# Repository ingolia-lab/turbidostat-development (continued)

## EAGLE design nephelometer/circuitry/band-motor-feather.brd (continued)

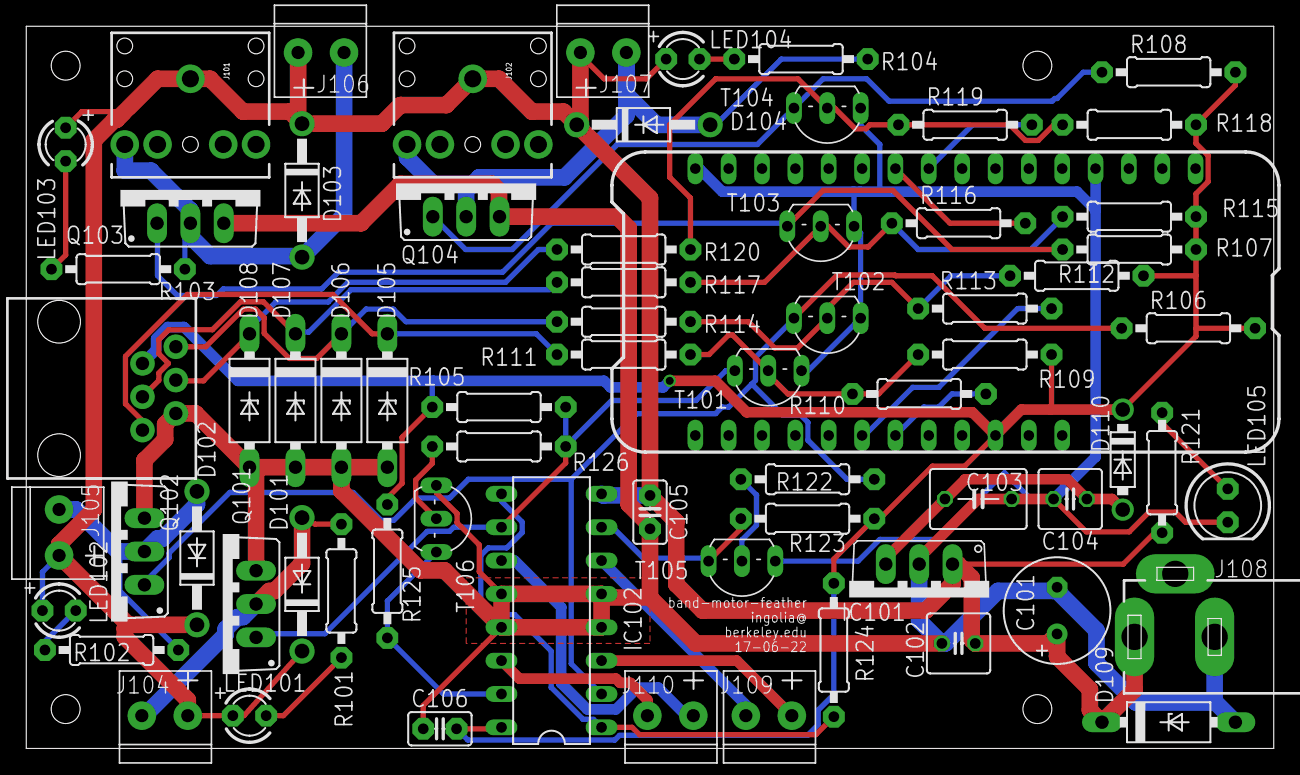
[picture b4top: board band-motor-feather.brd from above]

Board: 2 copper layers, 95.0 x 55.0 mm, 74 parts (0 on the bottom side), 38 nets.

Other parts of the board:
U$3, U$4, U$6, U$7: M2MOUNT

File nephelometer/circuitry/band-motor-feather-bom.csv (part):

"Part";"Value";"Device";"Package";"Description";"DIGIKEY#";"MANF";"MANF#";"MF";"MPN";"OC_FARNELL";"OC_NEWARK";
"C101";"220µF";"CPOL-USE3.5-8";"E3,5-8";"POLARIZED CAPACITOR, American symbol";"P5166-ND";"Panasonic Electronic Components";"ECA-1VM221";"";"";"";"";
"C102";"0.33µ";"C-US025-050X050";"C025-050X050";"CAPACITOR, American symbol";"445-5312-ND ";"TDK Corporation";"FK14X7R1H334K";"";"";"";"";
"C103";"22µ";"C-US050-045X075";"C050-045X075";"CAPACITOR, American symbol";"445-8455-ND";"TDK Corporation";"FK20X7R1C226M";"";"";"";"";
"C104";"0.33µ";"C-US025-050X050";"C025-050X050";"CAPACITOR, American symbol";"445-5312-ND ";"TDK Corporation";"FK14X7R1H334K";"";"";"";"";
"C105";"1µF";"C-US025-025X050";"C025-025X050";"CAPACITOR, American symbol";"445-5318-ND";"TDK Corporation";"FK14X7R1C105K";"";"";"";"";
"C106";"100nF";"C-US025-025X050";"C025-025X050";"CAPACITOR, American symbol";"BC1084CT-ND";"Vishay BC Components";"K104K15X7RF5TL2";"";"";"";"";
"D101";"1N4935";"1N4004";"DO41-10";"DIODE";"1N4935FSCT-ND";"Fairchild Semiconductor";"1N4935";"";"";"";"";
"D102";"1N4935";"1N4004";"DO41-10";"DIODE";"1N4935FSCT-ND";"Fairchild Semiconductor";"1N4935";"";"";"";"";
"D103";"1N4935";"1N4004";"DO41-10";"DIODE";"1N4935FSCT-ND";"Fairchild Semiconductor";"1N4935";"";"";"";"";
"D104";"1N4935";"1N4004";"DO41-10";"DIODE";"1N4935FSCT-ND";"Fairchild Semiconductor";"1N4935";"";"";"";"";
"D105";"";"ZENER-DIODEF126-10";"F126Z10";"Z-Diode";"SA5.0ALFCT-ND";"Littelfuse Inc.";"SA5.0A";"";"";"";"";
"D106";"";"ZENER-DIODEF126-10";"F126Z10";"Z-Diode";"SA5.0ALFCT-ND";"Littelfuse Inc.";"SA5.0A";"";"";"";"";
"D107";"";"ZENER-DIODEF126-10";"F126Z10";"Z-Diode";"SA5.0ALFCT-ND";"Littelfuse Inc.";"SA5.0A";"";"";"";"";
"D108";"";"ZENER-DIODEF126-10";"F126Z10";"Z-Diode";"SA5.0ALFCT-ND";"Littelfuse Inc.";"SA5.0A";"";"";"";"";
"D109";"";"ZENER-DIODEF126-10";"F126Z10";"Z-Diode";"SA12CALFCT-ND";"Littelfuse Inc.";"SA12CA";"";"";"";"";
"D110";"1N5817-T";"1N5817-T";"DO41-7.6";"1.0A SCHOTTKY BARRIER RECTIFIER";"1N5817FSCT-ND";"Fairchild Semiconductor";"1N5817";"";"";"";"";
"IC101";"7805TV";"7805TV";"TO220V";"Positive VOLTAGE REGULATOR";"LM7805CT-ND ";"Fairchild Semiconductor";"LM7805CT";"";"";"";"";
"IC102";"L293D";"L293D";"DIL16";"PUSH-PULL 4 CHANNEL DRIVER";"296-9518-5-ND";"Texas Instruments";"L293DNE";"";"L293D";"9589619";"56P8249";
"IC103";"FEATHER_M0";"FEATHER_M0";"FEATHER_M0";"";"2830-ND";"Adafruit Industries LLC";"2830";"";"";"";"";
"J101";"AUDIO-JACK2PTH";"AUDIO-JACK2PTH";"AUDIO-JACK";"Stereo audio jack with bypass switches.";"CP1-3523N-ND";"CUI Inc.";"SJ1-3523N";"";"";"";"";
"J102";"AUDIO-JACK2PTH";"AUDIO-JACK2PTH";"AUDIO-JACK";"Stereo audio jack with bypass switches.";"CP1-3523N-ND";"CUI Inc.";"SJ1-3523N";"";"";"";"";
"J103";"RJ11-6PTH";"RJ11-6PTH";"RJ11-6";"RJ11 Jack";"AE10383-ND";"Assmann WSW Components";"-2004-1-4-LP-N-R";"";"";"";"";
"J104";"MotA";"1X02_3.5MM_MOT";"1X02_3.5MM_MOT";"";"ED2740-ND";"On Shore Technology Inc.";"OSTTE020104";"";"";"";"";
"J105";"MotA";"1X02_3.5MM_MOT";"1X02_3.5MM_MOT";"";"ED2740-ND";"On Shore Technology Inc.";"OSTTE020104";"";"";"";"";
"J106";"MotA";"1X02_3.5MM_MOT";"1X02_3.5MM_MOT";"";"ED2740-ND";"On Shore Technology Inc.";"OSTTE020104";"";"";"";"";
"J107";"MotA";"1X02_3.5MM_MOT";"1X02_3.5MM_MOT";"";"ED2740-ND";"On Shore Technology Inc.";"OSTTE020104";"";"";"";"";
"J108";"PJ-102A";"PJ-102A";"PJ-102A";"";"CP-102A-ND";"CUI Inc.";"PJ-102A";"";"";"";"";
"J109";"MotA";"1X02_3.5MM_MOT";"1X02_3.5MM_MOT";"";"ED2740-ND";"On Shore Technology Inc.";"OSTTE020104";"";"";"";"";
"J110";"MotA";"1X02_3.5MM_MOT";"1X02_3.5MM_MOT";"";"ED2740-ND";"On Shore Technology Inc.";"OSTTE020104";"";"";"";"";
"LED101";"";"LED3MM";"LED3MM";"LED";"754-1275-ND";"Kingbright";"WP7113SRD/D";"";"";"";"";
"LED102";"";"LED3MM";"LED3MM";"LED";"754-1275-ND";"Kingbright";"WP7113SRD/D";"";"";"";"";
"LED103";"";"LED3MM";"LED3MM";"LED";"754-1275-ND";"Kingbright";"WP7113SRD/D";"";"";"";"";
"LED104";"";"LED3MM";"LED3MM";"LED";"754-1275-ND";"Kingbright";"WP7113SRD/D";"";"";"";"";
"LED105";"";"LED5MM";"LED5MM";"LED";"754-1735-ND";"Kingbright";"WP7113SGD";"";"";"";"";
"Q101";"";"IRLB8721";"TO220BV";"";"IRLB8721PBF-ND";"International Rectifier";"IRLB8721PBF";"";"";"";"";
"Q102";"";"IRLB8721";"TO220BV";"";"IRLB8721PBF-ND";"International Rectifier";"IRLB8721PBF";"";"";"";"";
"Q103";"";"IRLB8721";"TO220BV";"";"IRLB8721PBF-ND";"International Rectifier";"IRLB8721PBF";"";"";"";"";
"Q104";"";"IRLB8721";"TO220BV";"";"IRLB8721PBF-ND";"International Rectifier";"IRLB8721PBF";"";"";"";"";
"R101";"1K5";"R-US_0207/10";"0207/10";"RESISTOR, American symbol";"CF14JT1K50CT-ND";"Stackpole Electronics Inc";"CF14JT330R";"";"";"";"";
"R102";"1K5";"R-US_0207/10";"0207/10";"RESISTOR, American symbol";"CF14JT1K50CT-ND";"Stackpole Electronics Inc";"CF14JT330R";"";"";"";"";
"R103";"1K5";"R-US_0207/10";"0207/10";"RESISTOR, American symbol";"CF14JT1K50CT-ND";"Stackpole Electronics Inc";"CF14JT330R";"";"";"";"";
"R104";"1K5";"R-US_0207/10";"0207/10";"RESISTOR, American symbol";"CF14JT1K50CT-ND";"Stackpole Electronics Inc";"CF14JT330R";"";"";"";"";
"R105";"4K7";"R-US_0207/10";"0207/10";"RESISTOR, American symbol";"CF14JT4K70CT-ND";"Stackpole Electronics Inc";"CF14JT4K70";"";"";"";"";
"R106";"4K7";"R-US_0207/10";"0207/10";"RESISTOR, American symbol";"CF14JT4K70CT-ND";"Stackpole Electronics Inc";"CF14JT4K70";"";"";"";"";
"R107";"4K7";"R-US_0207/10";"0207/10";"RESISTOR, American symbol";"CF14JT4K70CT-ND";"Stackpole Electronics Inc";"CF14JT4K70";"";"";"";"";
"R108";"4K7";"R-US_0207/10";"0207/10";"RESISTOR, American symbol";"CF14JT4K70CT-ND";"Stackpole Electronics Inc";"CF14JT4K70";"";"";"";"";
"R109";"33K";"R-US_0207/10";"0207/10";"RESISTOR, American symbol";"CF14JT33K0CT-ND";"Stackpole Electronics Inc";"CF14JT33K0";"";"";"";"";
"R110";"2K2";"R-US_0207/10";"0207/10";"RESISTOR, American symbol";"CF14JT2K20CT-ND";"Stackpole Electronics Inc";"CF14JT2K20";"";"";"";"";
"R111";"680R";"R-US_0207/10";"0207/10";"RESISTOR, American symbol";"CF14JT680RCT-ND";"Stackpole Electronics Inc";"CF14JT680R";"";"";"";"";
"R112";"33K";"R-US_0207/10";"0207/10";"RESISTOR, American symbol";"CF14JT33K0CT-ND";"Stackpole Electronics Inc";"CF14JT33K0";"";"";"";"";
"R113";"2K2";"R-US_0207/10";"0207/10";"RESISTOR, American symbol";"CF14JT2K20CT-ND";"Stackpole Electronics Inc";"CF14JT2K20";"";"";"";"";
"R114";"680R";"R-US_0207/10";"0207/10";"RESISTOR, American symbol";"CF14JT680RCT-ND";"Stackpole Electronics Inc";"CF14JT680R";"";"";"";"";
"R115";"33K";"R-US_0207/10";"0207/10";"RESISTOR, American symbol";"CF14JT33K0CT-ND";"Stackpole Electronics Inc";"CF14JT33K0";"";"";"";"";
"R116";"2K2";"R-US_0207/10";"0207/10";"RESISTOR, American symbol";"CF14JT2K20CT-ND";"Stackpole Electronics Inc";"CF14JT2K20";"";"";"";"";
"R117";"680R";"R-US_0207/10";"0207/10";"RESISTOR, American symbol";"CF14JT680RCT-ND";"Stackpole Electronics Inc";"CF14JT680R";"";"";"";"";
"R118";"33K";"R-US_0207/10";"0207/10";"RESISTOR, American symbol";"CF14JT33K0CT-ND";"Stackpole Electronics Inc";"CF14JT33K0";"";"";"";"";
"R119";"2K2";"R-US_0207/10";"0207/10";"RESISTOR, American symbol";"CF14JT2K20CT-ND";"Stackpole Electronics Inc";"CF14JT2K20";"";"";"";"";
"R120";"680R";"R-US_0207/10";"0207/10";"RESISTOR, American symbol";"CF14JT680RCT-ND";"Stackpole Electronics Inc";"CF14JT680R";"";"";"";"";
"R121";"1K0";"R-US_0207/9";"0207/9";"RESISTOR, American symbol";"S1KHCT-ND";"Stackpole Electronics Inc.";"CFM12JT1K00";"";"";"";"";
"R122";"33K";"R-US_0207/10";"0207/10";"RESISTOR, American symbol";"CF14JT33K0CT-ND";"Stackpole Electronics Inc";"CF14JT33K0";"";"";"";"";
"R123";"10K";"R-US_0207/10";"0207/10";"RESISTOR, American symbol";"CF14JT10K0CT-ND";"Stackpole Electronics Inc";"CF14JT10K0";"";"";"";"";
"R124";"10K";"R-US_0207/10";"0207/10";"RESISTOR, American symbol";"CF14JT10K0CT-ND";"Stackpole Electronics Inc";"CF14JT10K0";"";"";"";"";
"R125";"10K";"R-US_0207/10";"0207/10";"RESISTOR, American symbol";"CF14JT10K0CT-ND";"Stackpole Electronics Inc";"CF14JT10K0";"";"";"";"";
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
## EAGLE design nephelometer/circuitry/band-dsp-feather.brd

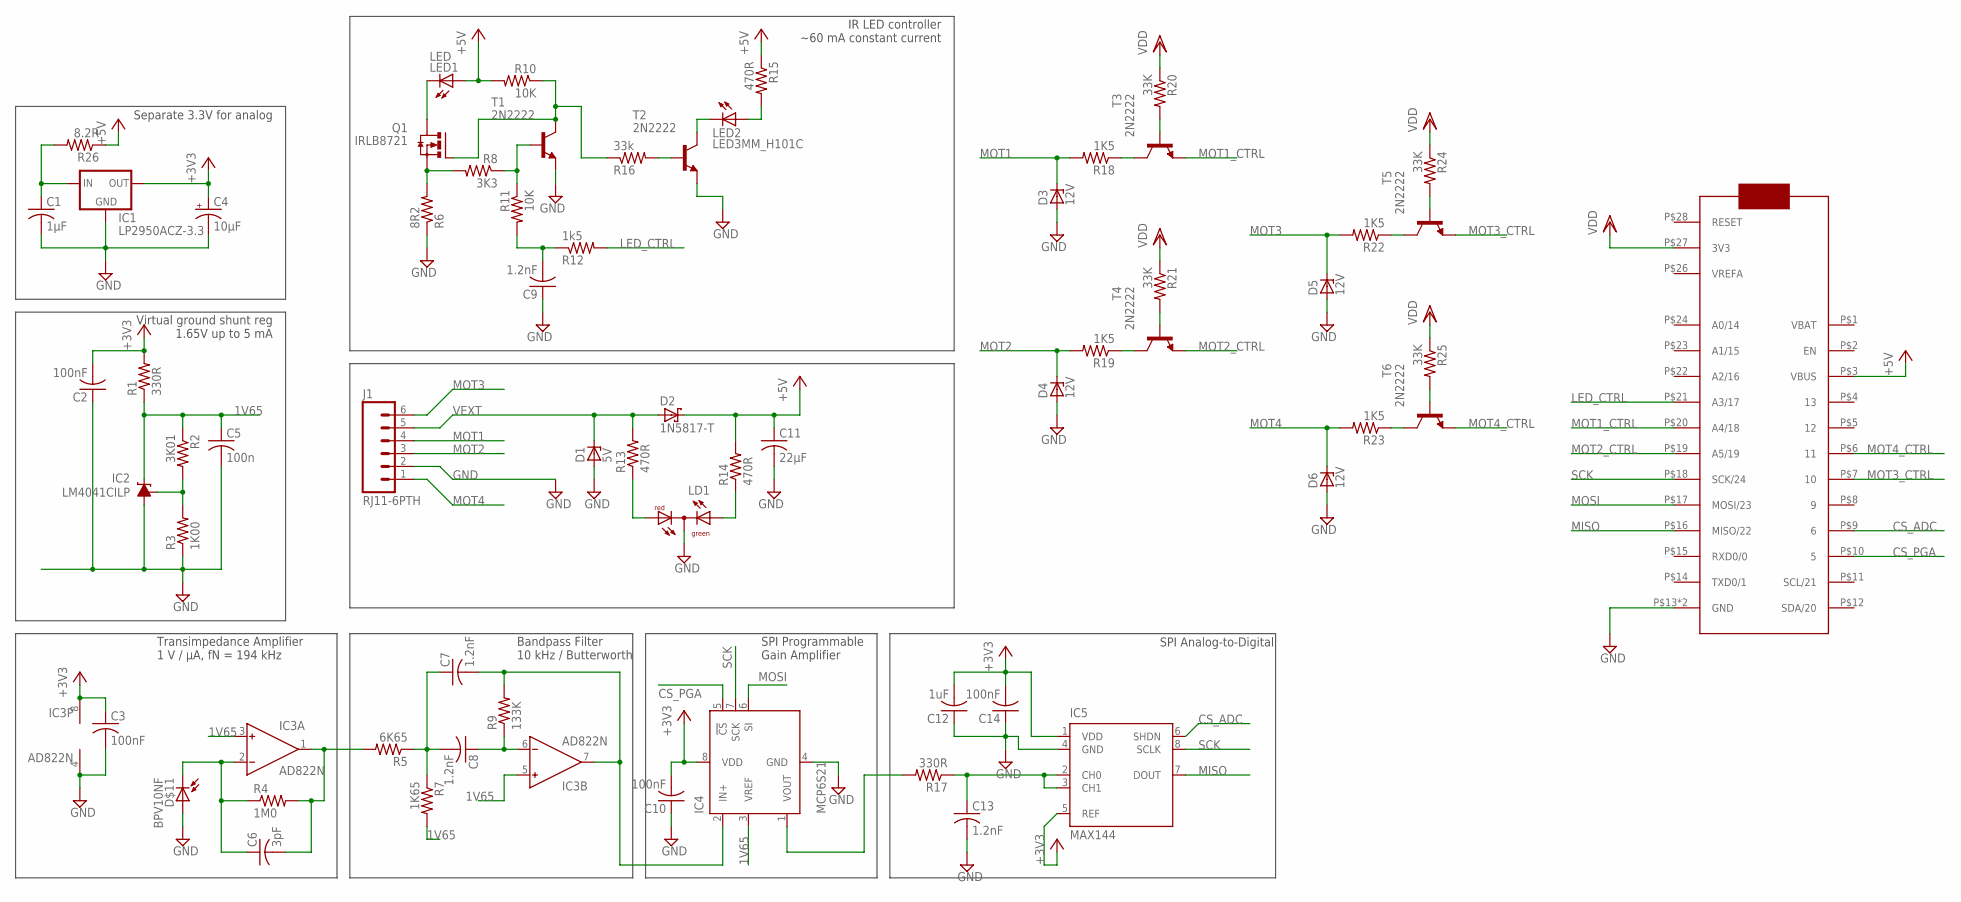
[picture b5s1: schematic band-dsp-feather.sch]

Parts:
C1: 1µF; C025-030X050; DIGIKEY# 445-5318-ND
C2, C3, C10, C14: 100nF; C025-025X050; DIGIKEY# BC1084CT-ND
C4: 10µF; E2,5-5; DIGIKEY# 478-8042-1-ND
C5: 100n; C025-025X050; DIGIKEY# BC1084CT-ND
C6: 3pF; C025-024X044; DIGIKEY# 445-8377-ND
C7, C8, C9, C13: 1.2nF; C025-025X050; DIGIKEY# BC1026CT-ND
C11: 22µF; C050-045X075; DIGIKEY# 445-8455-ND
C12: 1uF; C025-025X050; DIGIKEY# 445-5318-ND
D1: 5V; F126Z10; DIGIKEY# SA5.0ALFCT-ND
D2: 1N5817-T; DO41-7.6; DIGIKEY# 1N5817FSCT-ND
D3, D4, D5, D6: 12V; F126Z10; DIGIKEY# SA12CALFCT-ND
D$11: BPV10NF; LED5MM; DIGIKEY# 751-1002-ND
IC1: LP2950ACZ-3.3; TO92; DIGIKEY# LP2950ACZ-3.3/NOPB-ND
IC2: LM4041CILP; LP_O-PBCY-W3; DIGIKEY# 296-22173-1-ND
IC3: AD822N; DIL08; DIGIKEY# AD823ANZ-ND
IC4: MCP6S21; DIL08; DIGIKEY# MCP6S91-E/P-ND
IC5: MAX144; DIL08; DIGIKEY# MAX144ACPA+-ND
IC6: FEATHER_M0; DIGIKEY# 1528-1531-ND
J1: RJ11-6PTH; RJ11-6; DIGIKEY# AE10383-ND
LD1: DUOLED-RG-C; DUOLED-C-5MM; DIGIKEY# 754-1221-ND
LED1: LED; 1X02_3.5MM; DIGIKEY# 475-3002-ND
LED2: LED3MM_H101C; DIGIKEY# 754-1727-ND
Q1: IRLB8721; TO220BV; DIGIKEY# IRLB8721PBF-ND
R1: 330R; 0207/9; DIGIKEY# CF14JT330RCT-ND
R2: 3K01; 0207/9; DIGIKEY# RNF14FTD3K01CT-ND
R3: 1K00; 0207/9; DIGIKEY# RNF14FTD1K00CT-ND
R4: 1M0; 0207/9; DIGIKEY# RNV14FAL1M00CT-ND
R5: 6K65; 0207/9; DIGIKEY# 6.65KXBK-ND
R6: 8R2; 0207/9; DIGIKEY# S8.2HCT-ND
R7: 1K65; 0207/9; DIGIKEY# 1.65KXBK-ND
R8: 3K3; 0207/9; DIGIKEY# CF14JT3K30CT-ND
R9: 133K; 0207/9; DIGIKEY# 133KXBK-ND
R10, R11: 10K; 0207/9; DIGIKEY# CF14JT10K0CT-ND
R12: 1k5; 0207/9; DIGIKEY# CF14JT1K50CT-ND
R13, R14: 470R; 0207/9; DIGIKEY# CF14JT470RCT-ND
R15: 470R; 0207/5V; DIGIKEY# CF14JT470RCT-ND
R16: 33k; 0207/9; DIGIKEY# CF14JT33K0CT-ND
R17: 330R; 0207/9; DIGIKEY# S330CACT-ND
R18, R19, R22, R23: 1K5; 0207/9; DIGIKEY# CF14JT1K50CT-ND
R20, R21, R24, R25: 33K; 0207/9; DIGIKEY# CF14JT33K0CT-ND
R26: 8.2R; 0207/9; DIGIKEY# S8.2HCT-ND
T1, T2, T3, T4, T5, T6: 2N2222; TO92-EBC-OVAL; DIGIKEY# PN2222ATFCT-ND

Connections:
1V65: C5.1, IC2.2 (C), IC3.3 (IN+), IC3.5 (IN+), IC4.3 (VREF), R1.1, R2.1, R7.2
+3V3: C2.2, C3.1, C4.+, C10.2, C12.2, C14.2, IC1.1 (OUT), IC3.8 (V+), IC4.8 (VDD), IC5.1 (VDD), IC5.5 (REF), R1.2
+5V: C11.1, D2.C, IC6.P$3 (VBUS), LED1.1A (A), R10.2, R14.2, R15.1, R26.1
BPF: C7.2, IC3.7 (OUT), IC4.2 (IN+), R9.2
CS_ADC: IC5.6 (SHDN), IC6.P$9 (6)
CS_PGA: IC4.5 (!CS), IC6.P$10 (5)
FB: C6.1, D$11.K, IC3.2 (IN-), R4.1
GND: C1.2, C2.1, C3.2, C4.-, C5.2, C9.1, C10.1, C11.2, C12.1, C13.2, C14.1, D1.A, D3.A, D4.A, D5.A, D6.A, D$11.A, IC1.2 (GND), IC2.3 (A), IC3.4 (V-), IC4.4 (GND), IC5.4 (GND), IC6.P$13 (GND), IC6.P$25 (GND), J1.2, LD1.C, R3.1, R6.1, T1.E, T2.E
LED_CTRL: IC6.P$21 (A3/17), R12.2
MISO: IC5.7 (DOUT), IC6.P$16 (MISO/22)
MOSI: IC4.6 (SI), IC6.P$17 (MOSI/23)
MOT1: D3.C, J1.4, R18.2
MOT1_CTRL: IC6.P$20 (A4/18), T3.E
MOT2: D4.C, J1.3, R19.2
MOT2_CTRL: IC6.P$19 (A5/19), T4.E
MOT3: D5.C, J1.6, R22.2
MOT3_CTRL: IC6.P$7 (10), T5.E
MOT4: D6.C, J1.1, R23.2
MOT4_CTRL: IC6.P$6 (11), T6.E
unnamed: R19.1, T4.C
unnamed: R21.2, T4.B
unnamed: C7.1, C8.2, R5.1, R7.1
unnamed: IC4.1 (VOUT), R17.2
unnamed: R22.1, T5.C
unnamed: R24.2, T5.B
unnamed: LD1.AX (AG), R14.1
unnamed: Q1.G, R10.1, R16.1, T1.C
unnamed: C8.1, IC3.6 (IN-), R9.1
unnamed: R23.1, T6.C
unnamed: LED2.A, R15.2
unnamed: LED2.K, T2.C
unnamed: R8.1, R11.1, T1.B
unnamed: Q1.S, R6.2, R8.2
unnamed: C9.2, R11.2, R12.1
unnamed: R16.2, T2.B
unnamed: LED1.2K (K), Q1.D
unnamed: R18.1, T3.C
unnamed: R20.2, T3.B
unnamed: R25.2, T6.B
unnamed: LD1.AR, R13.1
unnamed: C13.1, IC5.2 (CH0), IC5.3 (CH1), R17.1
unnamed: C1.1, IC1.3 (IN), R26.2
unnamed: IC2.1 (FB), R2.2, R3.2
SCK: IC4.7 (SCK), IC5.8 (SCLK), IC6.P$18 (SCK/24)
TIA: C6.2, IC3.1 (OUT), R4.2, R5.2
VDD: IC6.P$27 (3V3), R20.1, R21.1, R24.1, R25.1
VEXT: D1.C, D2.A, J1.5, R13.2

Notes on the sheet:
Transimpedance Amplifier 1 V / µA, fN = 194 kHz
Bandpass Filter 10 kHz / Butterworth
Virtual ground shunt reg 1.65V up to 5 mA
IR LED controller ~60 mA constant current
SPI Programmable Gain Amplifier
Separate 3.3V for analog
SPI Analog-to-Digital

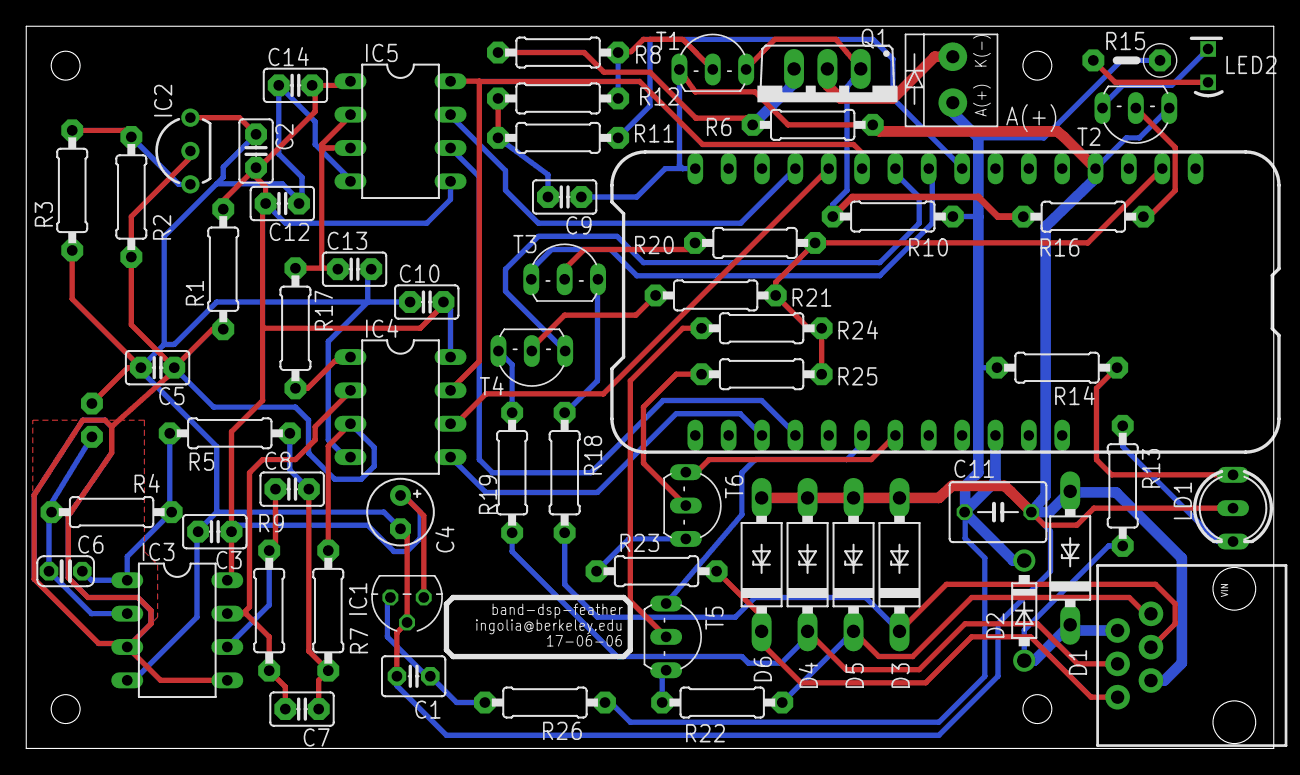
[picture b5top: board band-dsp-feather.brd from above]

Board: 2 copper layers, 95.0 x 55.0 mm, 68 parts (1 on the bottom side), 47 nets.

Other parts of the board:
U$1, U$2, U$3, U$4: M2MOUNT

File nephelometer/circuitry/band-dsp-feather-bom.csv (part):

"Part";"Value";"Device";"Package";"Description";"DIGIKEY#";"DIGIKEY2#";"DIGIKEY3#";"MANF";"MANF#";"MANF2";"MANF2#";"MANF3";"MANF3#";"MF";"MPN";"OC_FARNELL";"OC_NEWARK";
"C1";"1µF";"C-US025-030X050";"C025-030X050";"CAPACITOR, American symbol";"445-5318-ND";"";"";"TDK Corporation";"FK14X7R1C105K";"";"";"";"";"";"";"";"";
"C2";"100nF";"C-US025-025X050";"C025-025X050";"CAPACITOR, American symbol";"BC1084CT-ND";"";"";"Vishay BC Components";"K104K15X7RF5TL2";"";"";"";"";"";"";"";"";
"C3";"100nF";"C-US025-025X050";"C025-025X050";"CAPACITOR, American symbol";"BC1084CT-ND";"";"";"Vishay BC Components";"K104K15X7RF5TL2";"";"";"";"";"";"";"";"";
"C4";"10µF";"CPOL-USE2.5-5";"E2,5-5";"POLARIZED CAPACITOR, American symbol";"478-8042-1-ND";"";"";"AVX Corporation";"TAP106K016SRW";"";"";"";"";"";"";"";"";
"C5";"100n";"C-US025-025X050";"C025-025X050";"CAPACITOR, American symbol";"BC1084CT-ND";"";"";"Vishay BC Components";"K104K15X7RF5TL2";"";"";"";"";"";"";"";"";
"C6";"3pF";"C-US025-024X044";"C025-024X044";"CAPACITOR, American symbol";"445-8377-ND";"";"";"TDK Corporation";"FK18C0G1H030C";"";"";"";"";"";"";"";"";
"C7";"1.2nF";"C-US025-025X050";"C025-025X050";"CAPACITOR, American symbol";"BC1026CT-ND";"";"";"Vishay BC Components";"K122J15C0GF5TL2";"";"";"";"";"";"";"";"";
"C8";"1.2nF";"C-US025-025X050";"C025-025X050";"CAPACITOR, American symbol";"BC1026CT-ND";"";"";"Vishay BC Components";"K122J15C0GF5TL2";"";"";"";"";"";"";"";"";
"C9";"1.2nF";"C-US025-025X050";"C025-025X050";"CAPACITOR, American symbol";"BC1026CT-ND";"";"";"Vishay BC Components";"K122J15C0GF5TL2";"";"";"";"";"";"";"";"";
"C10";"100nF";"C-US025-025X050";"C025-025X050";"CAPACITOR, American symbol";"BC1084CT-ND";"";"";"Vishay BC Components";"K104K15X7RF5TL2";"";"";"";"";"";"";"";"";
"C11";"22µF";"C-US050-045X075";"C050-045X075";"CAPACITOR, American symbol";"445-8455-ND";"";"";"TDK Corporation";"FK20X7R1C226M";"";"";"";"";"";"";"";"";
"C12";"1uF";"C-US025-025X050";"C025-025X050";"CAPACITOR, American symbol";"445-5318-ND";"";"";"TDK Corporation";"FK14X7R1C105K";"";"";"";"";"";"";"";"";
"C13";"1.2nF";"C-US025-025X050";"C025-025X050";"CAPACITOR, American symbol";"BC1026CT-ND";"";"";"Vishay BC Components";"K122J15C0GF5TL2";"";"";"";"";"";"";"";"";
"C14";"100nF";"C-US025-025X050";"C025-025X050";"CAPACITOR, American symbol";"BC1084CT-ND";"";"";"Vishay BC Components";"K104K15X7RF5TL2";"";"";"";"";"";"";"";"";
"D$11";"BPV10NF";"BPV10NF";"LED5MM";"";"751-1002-ND";"";"";"Vishay Semiconductor Opto Division";"BPV10NF";"";"";"";"";"";"";"";"";
"D1";"5V";"ZENER-DIODEF126-10";"F126Z10";"Z-Diode";"SA5.0ALFCT-ND";"";"";"Littelfuse Inc.";"SA5.0A";"";"";"";"";"";"";"";"";
"D2";"1N5817-T";"1N5817-T";"DO41-7.6";"1.0A SCHOTTKY BARRIER RECTIFIER";"1N5817FSCT-ND";"";"";"Fairchild Semiconductor";"1N5817";"";"";"";"";"";"";"";"";
"D3";"12V";"ZENER-DIODEF126-10";"F126Z10";"Z-Diode";"SA12ALFCT-ND";"";"";"Littelfuse Inc.";"SA12A";"";"";"";"";"";"";"";"";
"D4";"12V";"ZENER-DIODEF126-10";"F126Z10";"Z-Diode";"SA12ALFCT-ND";"";"";"Littelfuse Inc.";"SA12A";"";"";"";"";"";"";"";"";
"D5";"12V";"ZENER-DIODEF126-10";"F126Z10";"Z-Diode";"SA12ALFCT-ND";"";"";"Littelfuse Inc.";"SA12A";"";"";"";"";"";"";"";"";
"D6";"12V";"ZENER-DIODEF126-10";"F126Z10";"Z-Diode";"SA12ALFCT-ND";"";"";"Littelfuse Inc.";"SA12A";"";"";"";"";"";"";"";"";
"IC1";"LP2950ACZ-3.3";"LP2950ACZ-3.3";"TO92";"Source: http://cache.national.com/ds/LP/LP2950.pdf";"LP2950ACZ-3.3/NOPB-ND";"";"";"Texas Instruments";"LP2950ACZ-3.3/NOPB";"";"";"";"";"";"";"";"";
"IC2";"LM4041CILP";"LM4041CILP";"LP_O-PBCY-W3";"PRECISION MICROPOWER SHUNT VOLTAGE REFERENCE Adjustable Output";"296-22173-1-ND";"";"";"Texas Instruments";"LM4041CILPR";"";"";"";"";"";"LM4041CILP";"1673945";"50M8856";
"IC3";"AD822N";"AD822N";"DIL08";"Single-Supply, Rail-to-Rail Low Power FET-Input Op Amp";"AD823ANZ-ND";"";"";"Analog Devices Inc.";"AD823ANZ";"";"";"";"";"";"";"1438581";"unknown";
"IC4";"MCP6S21";"MCP6S21";"DIL08";"";"MCP6S91-E/P-ND";"";"";"Microchip Technology";"MCP6S91-E/P";"";"";"";"";"";"";"";"";
"IC5";"MAX144";"MAX144";"DIL08";"";"MAX144ACPA+-ND";"";"";"Maxim Integrated";"MAX144ACPA+";"";"";"";"";"";"";"";"";
"IC6";"FEATHER_M0";"FEATHER_M0";"FEATHER_M0";"";"1528-1531-ND";"2830-ND";"";"Adafruit Industries LLC";"2772";"Adafruit Industries LLC";"2830";"";"";"";"";"";"";
"J1";"RJ11-6PTH";"RJ11-6PTH";"RJ11-6";"RJ11 Jack";"AE10383-ND";"";"";"Assmann WSW Components";"A-2004-1-4-LP-N-R";"";"";"";"";"";"";"";"";
"LD1";"";"DUOLED-RG-C";"DUOLED-C-5MM";"DUO LED";"754-1221-ND";"";"";"Kingbright";"WP3VEGW";"";"";"";"";"";"";"";"";
"LED1";"LED";"1X02_3.5MM_LED";"1X02_3.5MM";"";"475-3002-ND";"492-1502-ND";"ED2740-ND";"OSRAM Opto Semiconductors Inc";"SFH 4547";"Bivar Inc";"CR-174";"On Shore Technology Inc.";"OSTTE020104";"";"";"";"";
"LED2";"LED3MM_H101C";"LED3MM_H101C";"LED3MM_H101C";"";"754-1727-ND";"492-1789-ND";"";"Kingbright";"WP710A10SYD";"Bivar Inc.";"H-101C";"";"";"";"";"";"";
"Q1";"IRLB8721";"IRLB8721";"TO220BV";"";"IRLB8721PBF-ND";"";"";"Infineon Technologies";"IRLB8721PBF";"";"";"";"";"";"";"";"";
"R1";"330R";"R-US_0207/9";"0207/9";"RESISTOR, American symbol";"CF14JT330RCT-ND";"";"";"Stackpole Electronics Inc.";"CF14JT330R";"";"";"";"";"";"";"";"";
"R2";"3K01";"R-US_0207/9";"0207/9";"RESISTOR, American symbol";"RNF14FTD3K01CT-ND";"";"";"Stackpole Electronics Inc.";"RNF14FTD3K01";"";"";"";"";"";"";"";"";
"R3";"1K00";"R-US_0207/9";"0207/9";"RESISTOR, American symbol";"RNF14FTD1K00CT-ND";"";"";"Stackpole Electronics Inc.";"RNF14FTD1K00";"";"";"";"";"";"";"";"";
"R4";"1M0";"R-US_0207/9";"0207/9";"RESISTOR, American symbol";"RNV14FAL1M00CT-ND";"";"";"Stackpole Electronics Inc";"RNV14FAL1M00";"";"";"";"";"";"";"";"";
"R5";"6K65";"R-US_0207/9";"0207/9";"RESISTOR, American symbol";"6.65KXBK-ND";"";"";"Yageo";"MFR-25FBF52-6K65";"";"";"";"";"";"";"";"";
"R6";"8R2";"R-US_0207/9";"0207/9";"RESISTOR, American symbol";"S8.2HCT-ND";"";"";"Stackpole Electronics Inc.";"CFM12JT8R20";"";"";"";"";"";"";"";"";
"R7";"1K65";"R-US_0207/9";"0207/9";"RESISTOR, American symbol";"1.65KXBK-ND";"";"";"Yageo";"MFR-25FBF52-1K65";"";"";"";"";"";"";"";"";
"R8";"3K3";"R-US_0207/9";"0207/9";"RESISTOR, American symbol";"CF14JT3K30CT-ND";"";"";"Stackpole Electronics Inc";"CF14JT3K30";"";"";"";"";"";"";"";"";
"R9";"133K";"R-US_0207/9";"0207/9";"RESISTOR, American symbol";"133KXBK-ND";"";"";"Yageo";"MFR-25FBF52-133K";"";"";"";"";"";"";"";"";
"R10";"10K";"R-US_0207/9";"0207/9";"RESISTOR, American symbol";"CF14JT10K0CT-ND";"";"";"Stackpole Electronics Inc";"CF14JT10K0";"";"";"";"";"";"";"";"";
"R11";"10K";"R-US_0207/9";"0207/9";"RESISTOR, American symbol";"CF14JT10K0CT-ND";"";"";"Stackpole Electronics Inc";"CF14JT10K0";"";"";"";"";"";"";"";"";
"R12";"1k5";"R-US_0207/9";"0207/9";"RESISTOR, American symbol";"CF14JT1K50CT-ND";"";"";"Stackpole Electronics Inc";"CF14JT1K50";"";"";"";"";"";"";"";"";
"R13";"470R";"R-US_0207/9";"0207/9";"RESISTOR, American symbol";"CF14JT470RCT-ND";"";"";"Stackpole Electronics Inc.";"CF14JT470R";"";"";"";"";"";"";"";"";
"R14";"470R";"R-US_0207/9";"0207/9";"RESISTOR, American symbol";"CF14JT470RCT-ND";"";"";"Stackpole Electronics Inc.";"CF14JT470R";"";"";"";"";"";"";"";"";
"R15";"470R";"R-US_0207/5V";"0207/5V";"RESISTOR, American symbol";"CF14JT470RCT-ND";"";"";"Stackpole Electronics Inc.";"CF14JT470R";"";"";"";"";"";"";"";"";
"R16";"33k";"R-US_0207/9";"0207/9";"RESISTOR, American symbol";"CF14JT33K0CT-ND";"";"";"Stackpole Electronics Inc";"CF14JT33K0";"";"";"";"";"";"";"";"";
"R17";"330R";"R-US_0207/9";"0207/9";"RESISTOR, American symbol";"S330CACT-ND";"";"";"Stackpole Electronics Inc.";"RNMF14FTC330R";"";"";"";"";"";"";"";"";
"R18";"1K5";"R-US_0207/9";"0207/9";"RESISTOR, American symbol";"CF14JT1K50CT-ND";"";"";"Stackpole Electronics Inc.";"CF14JT1K50";"";"";"";"";"";"";"";"";
"R19";"1K5";"R-US_0207/9";"0207/9";"RESISTOR, American symbol";"CF14JT1K50CT-ND";"";"";"Stackpole Electronics Inc.";"CF14JT1K50";"";"";"";"";"";"";"";"";
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
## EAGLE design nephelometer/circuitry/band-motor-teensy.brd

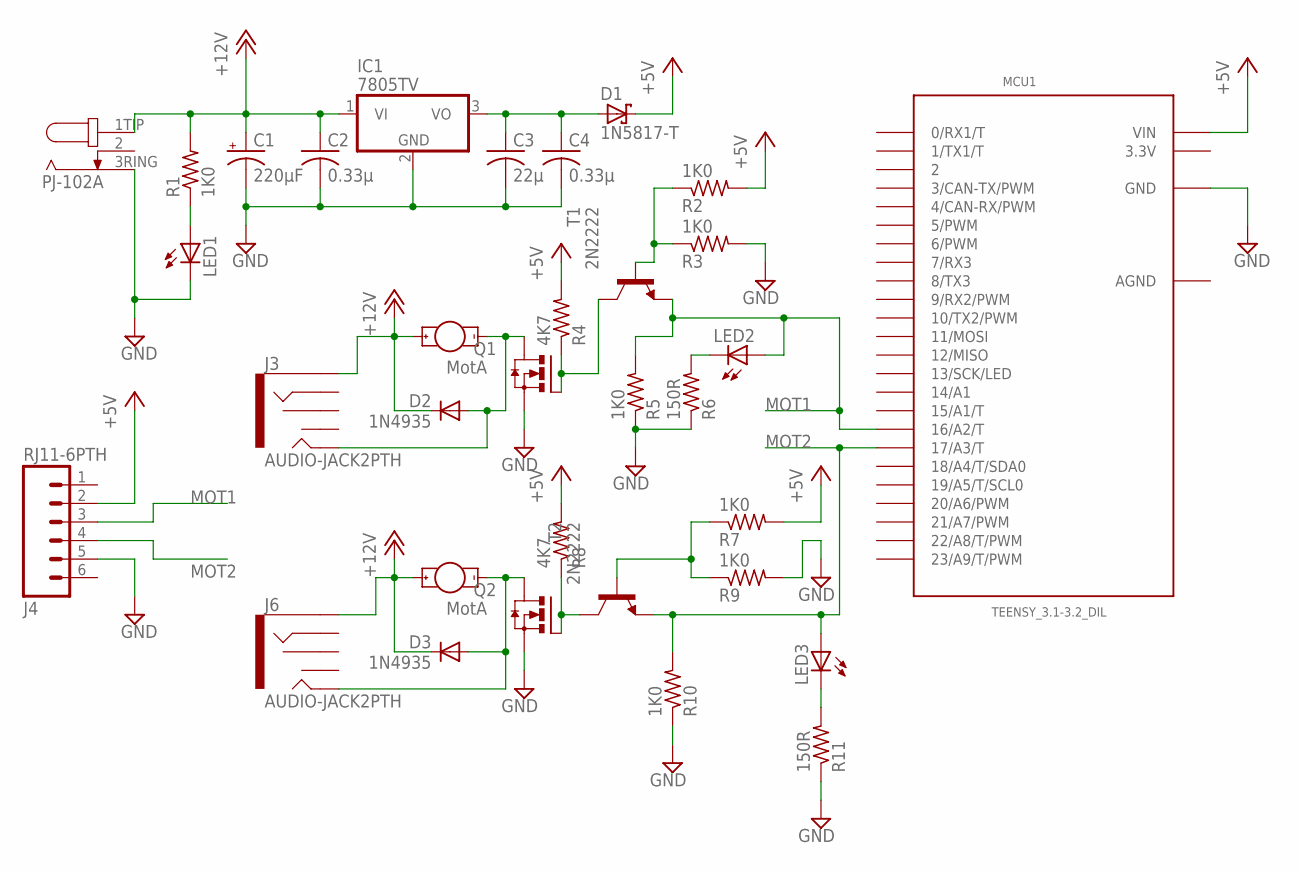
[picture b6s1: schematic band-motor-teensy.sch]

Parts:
C1: 220µF; E3,5-8; DIGIKEY# P5166-ND
C2, C4: 0.33µ; C025-050X050; DIGIKEY# 445-5312-ND
C3: 22µ; C050-045X075; DIGIKEY# 445-8455-ND
D1: 1N5817-T; DO41-7.6; DIGIKEY# 1N5817FSCT-ND
D2, D3: 1N4935; DO41-10; DIGIKEY# 1N4935FSCT-ND
IC1: 7805TV; TO220V; DIGIKEY# LM7805CT-ND
J1: PJ-102A
J2, J5: MotA; 1X02_3.5MM_MOT; DIGIKEY# SC1455-ND
J3, J6: AUDIO-JACK2PTH; AUDIO-JACK
J4: RJ11-6PTH; RJ11-6
LED1: LED5MM; DIGIKEY# 754-1735-ND
LED2, LED3: LED3MM; DIGIKEY# 754-1275-ND
MCU1: TEENSY_3.1-3.2_DIL; TEENSY_3.0-3.2&LC_DIL
Q1, Q2: IRLB8721; TO220BV; DIGIKEY# IRLU120NPBF-ND
R1: 1K0; 0207/9; DIGIKEY# S1KHCT-ND
R2, R3, R5, R7, R9, R10: 1K0; 0207/10; DIGIKEY# CF14JT150RCT-ND
R4, R8: 4K7; 0207/10; DIGIKEY# CF14JT150RCT-ND
R6, R11: 150R; 0207/10; DIGIKEY# CF14JT150RCT-ND
T1, T2: 2N2222; TO92-EBC-OVAL

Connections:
3.3V: MCU1.3.3V
+5V: D1.C, J4.2, MCU1.VIN, R2.2, R4.2, R7.2, R8.2
+12V: C1.+, C2.1, D2.C, D3.C, IC1.1 (VI), J1.1TIP (3TIP), J2.1A (+), J3.SLEEVE, J5.1A (+), J6.SLEEVE, R1.2
AGND: MCU1.AGND
GND: C1.-, C2.2, C3.2, C4.2, IC1.2 (GND), J1.3RING (1RING), J4.5, LED1.K (C), MCU1.GND, Q1.S, Q2.S, R3.2, R5.1, R6.1, R9.2, R10.1, R11.1
MOT1: J4.3, LED2.A, MCU1.16/A2 (16/A2/T), R5.2, T1.E
MOT2: J4.4, LED3.A, MCU1.17/A3 (17/A3/T), R10.2, T2.E
unnamed: LED1.A, R1.1
unnamed: C3.1, C4.1, D1.A, IC1.3 (VO)
unnamed: D3.A, J5.2K (-), J6.TIP, Q2.D
unnamed: D2.A, J2.2K (-), J3.TIP, Q1.D
unnamed: LED2.K (C), R6.2
unnamed: R2.1, R3.1, T1.B
unnamed: R7.1, R9.1, T2.B
unnamed: Q1.G, R4.1, T1.C
unnamed: Q2.G, R8.1, T2.C
unnamed: LED3.K (C), R11.2

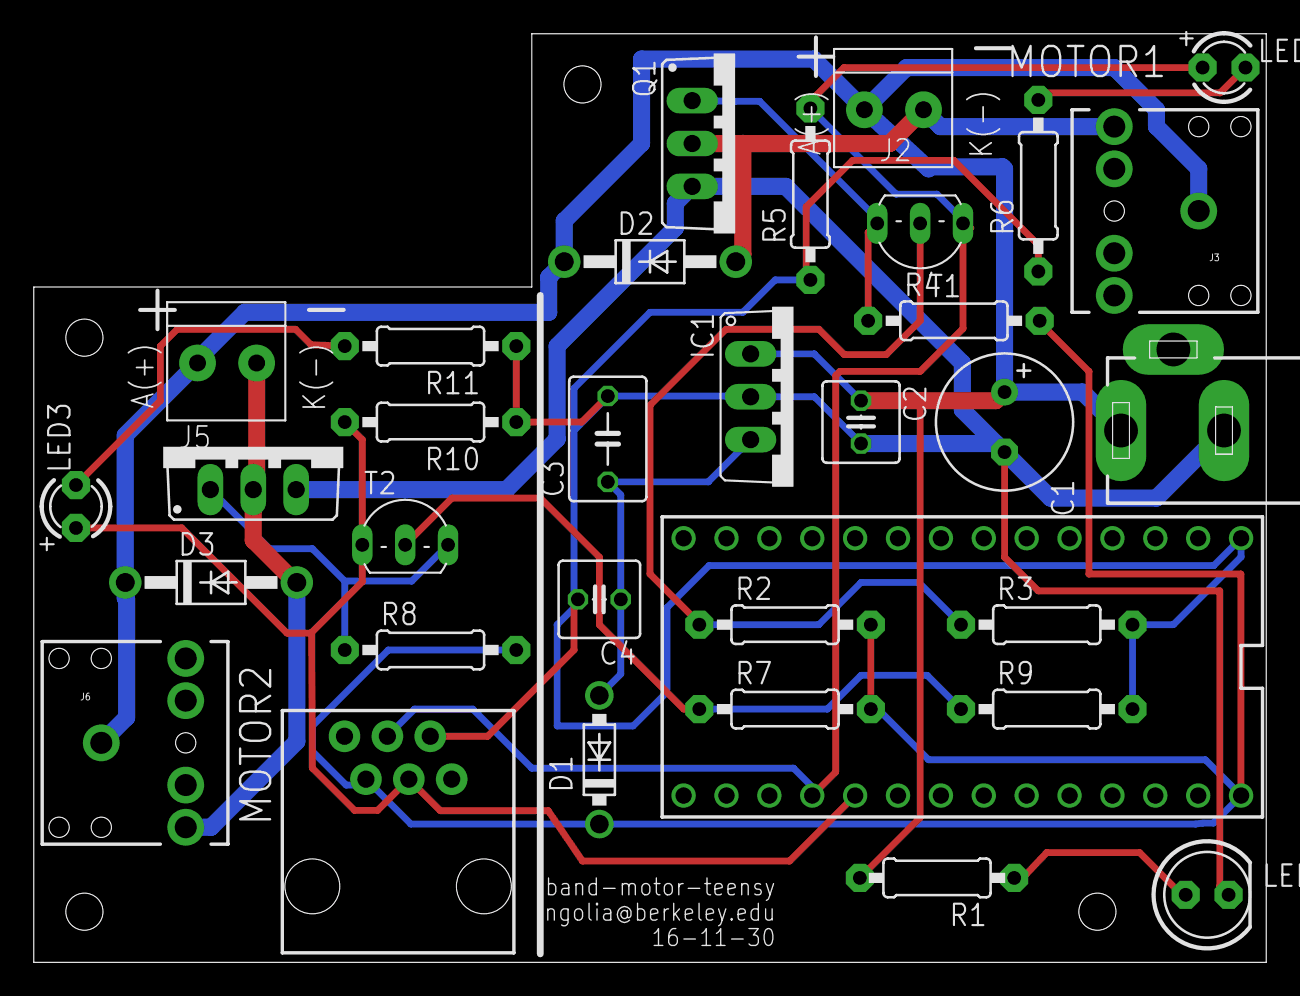
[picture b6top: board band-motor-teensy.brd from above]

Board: 2 copper layers, 73.0 x 55.0 mm, 37 parts (0 on the bottom side), 15 nets.

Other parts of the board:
U$3, U$4, U$6, U$7: M2MOUNT
